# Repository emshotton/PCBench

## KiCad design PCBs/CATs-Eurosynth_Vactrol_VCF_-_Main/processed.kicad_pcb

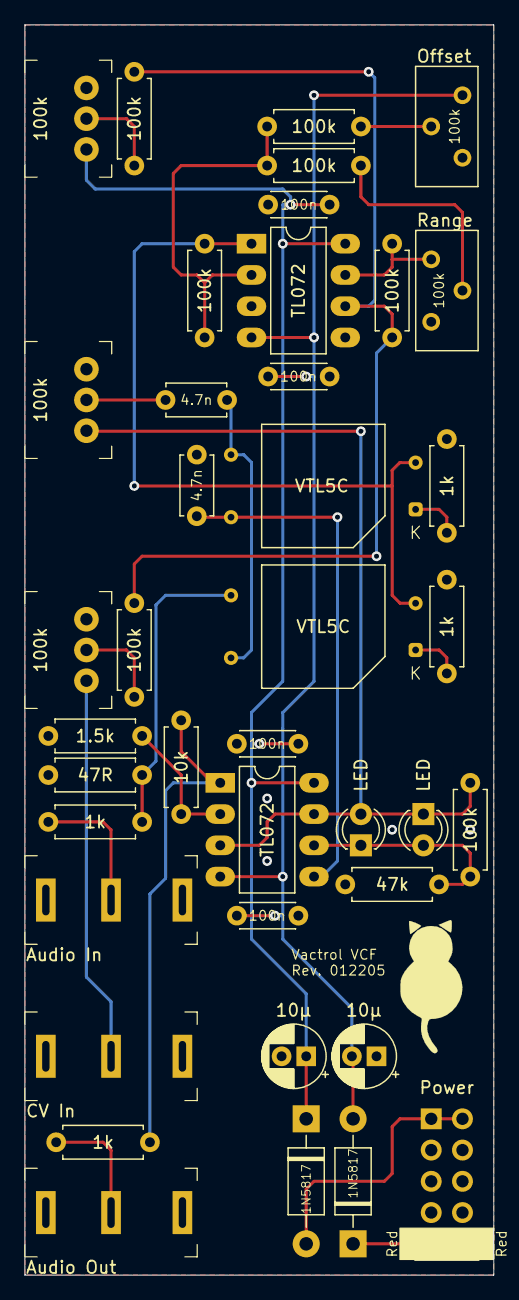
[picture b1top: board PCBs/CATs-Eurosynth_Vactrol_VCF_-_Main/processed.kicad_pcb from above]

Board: 2 copper layers, 38.1 x 101.6 mm, 40 parts (0 on the bottom side), 26 nets.

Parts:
C1, C2: 4.7n; C_Disc_D4.7mm_W2.5mm_P5.00mm
C3, C4: 10µ; CP_Radial_D5.0mm_P2.00mm
C5, C6, C7, C8: 100n; C_Disc_D4.3mm_W1.9mm_P5.00mm
D1, D2: LED; LED_D3.0mm
D3, D4: 1N5817; D_DO-41_SOD81_P10.16mm_Horizontal
J1: Audio In; Jack_3.5mm_QingPu_WQP-PJ323M
J2: Audio Out; Jack_3.5mm_QingPu_WQP-PJ323M
J3: Power; Power_2x5_Vertical
J4: CV In; Jack_3.5mm_QingPu_WQP-PJ323M
P1, P2, P3: 100k; Potentiometer_AlpsAlpine_RK0971110
R1, R3, R4, R12: 1k; R_Axial_DIN0207_L6.3mm_D2.5mm_P7.62mm_Horizontal
R2: 47R; R_Axial_DIN0207_L6.3mm_D2.5mm_P7.62mm_Horizontal
R5: 47k; R_Axial_DIN0207_L6.3mm_D2.5mm_P7.62mm_Horizontal
R6, R7, R8, R9, R13, R14, R15: 100k; R_Axial_DIN0207_L6.3mm_D2.5mm_P7.62mm_Horizontal
R10: 1.5k; R_Axial_DIN0207_L6.3mm_D2.5mm_P7.62mm_Horizontal
R11: 10k; R_Axial_DIN0207_L6.3mm_D2.5mm_P7.62mm_Horizontal
RV1, RV2: 100k; Potentiometer_Bourns_3296Y_Vertical
U1, U2: VTL5C; PerkinElmer_VTL5C
U3, U4: TL072; DIP-8_W7.62mm_LongPads

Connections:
+12V: C3.1, C5.1, C7.1, D3.1, P2.CW, U3.8, U4.8
-12V: C4.2, C6.2, C8.2, D4.2, RV1.3, U3.4, U4.4
GND: C2.1, C3.2, C4.1, C5.2, C6.1, C7.2, C8.1, J1.S, J1.TN, J2.S, J3.GND, J4.S, J4.TN, P1.CCW, P2.CCW, P3.CCW, R2.2, R3.1, R4.1, R5.1, R10.1, RV1.1, RV2.3, U3.3, U3.5
unnamed: C1.1, P1.W
unnamed: C1.2, U1.3, U2.4
unnamed: C2.2, U2.3, U4.5
unnamed: D1.1, D2.2, R5.2, R7.2, U4.6
unnamed: D1.2, D2.1, P1.CW, R7.1, U4.3, U4.7
unnamed: D3.2, J3.+12V
unnamed: D4.1, J3.-12V
unnamed: J1.T, R1.2
unnamed: J2.T, R12.1
unnamed: J4.T, P3.CW
unnamed: P2.W, R14.1
unnamed: P3.W, R15.1
unnamed: R1.1, R2.1, U1.4
unnamed: R3.2, U1.1
unnamed: R4.2, U2.1
unnamed: R6.1, R8.2, R9.2, U3.2
unnamed: R6.2, U1.2, U2.2, U3.1
unnamed: R8.1, RV1.2
unnamed: R9.1, RV2.2
unnamed: R10.2, R11.2, U4.2
unnamed: R11.1, R12.2, U4.1
unnamed: R13.1, R14.2, R15.2, U3.6
unnamed: R13.2, RV2.1, U3.7

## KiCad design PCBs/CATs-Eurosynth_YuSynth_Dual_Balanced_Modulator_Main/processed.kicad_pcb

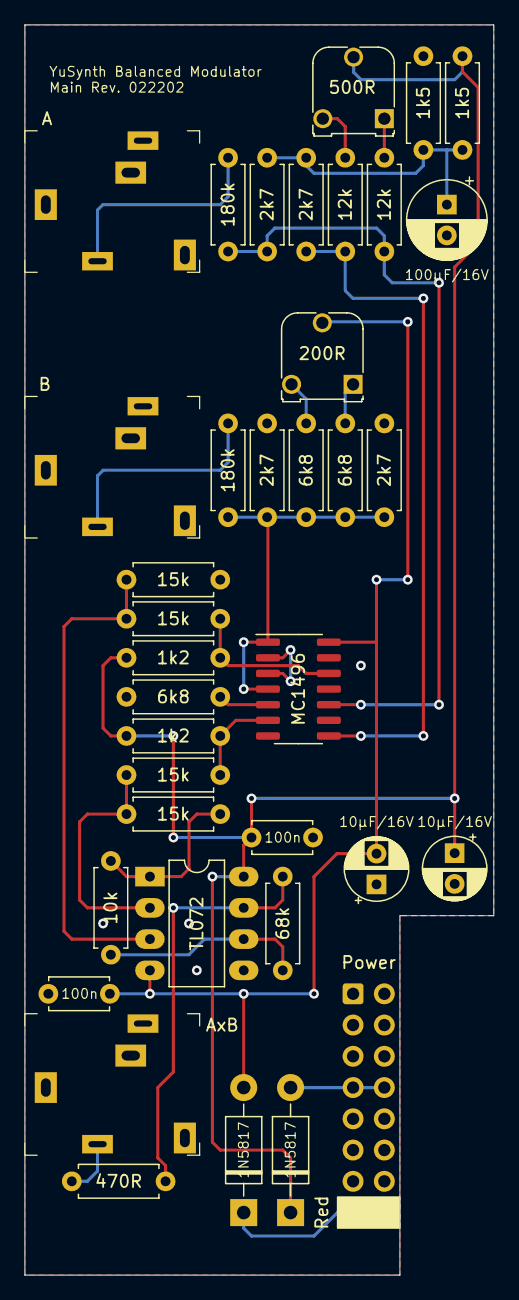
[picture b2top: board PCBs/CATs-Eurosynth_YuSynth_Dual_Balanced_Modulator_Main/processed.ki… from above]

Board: 2 copper layers, 38.1 x 101.6 mm, 37 parts (0 on the bottom side), 25 nets.

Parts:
C1: 100µF/16V; CP_Radial_D6.3mm_P2.50mm
C2, C3: 10µF/16V; CP_Radial_D5.0mm_P2.50mm
C4, C5: 100n; C_Disc_D4.7mm_W2.5mm_P5.00mm
D1, D2: 1N5817; D_DO-41_SOD81_P10.16mm_Horizontal
J1: Power; Power_2x8_Horizontal
J2: A; Jack_3.5mm_QingPu_WQP-PJ324M
J3: B; Jack_3.5mm_QingPu_WQP-PJ324M
J4: AxB; Jack_3.5mm_QingPu_WQP-PJ324M
R1, R2: 1k5; R_Axial_DIN0207_L6.3mm_D2.5mm_P7.62mm_Horizontal
R3, R4: 180k; R_Axial_DIN0207_L6.3mm_D2.5mm_P7.62mm_Horizontal
R5, R7, R8, R12: 2k7; R_Axial_DIN0207_L6.3mm_D2.5mm_P7.62mm_Horizontal
R6, R10, R14: 6k8; R_Axial_DIN0207_L6.3mm_D2.5mm_P7.62mm_Horizontal
R9, R11: 12k; R_Axial_DIN0207_L6.3mm_D2.5mm_P7.62mm_Horizontal
R13, R15: 1k2; R_Axial_DIN0207_L6.3mm_D2.5mm_P7.62mm_Horizontal
R16, R17, R18, R19: 15k; R_Axial_DIN0207_L6.3mm_D2.5mm_P7.62mm_Horizontal
R20: 10k; R_Axial_DIN0207_L6.3mm_D2.5mm_P7.62mm_Horizontal
R21: 68k; R_Axial_DIN0207_L6.3mm_D2.5mm_P7.62mm_Horizontal
R22: 470R; R_Axial_DIN0207_L6.3mm_D2.5mm_P7.62mm_Horizontal
RV1: 200R; Potentiometer_Runtron_RM-065_Vertical
RV2: 500R; Potentiometer_Runtron_RM-065_Vertical
U1: MC1496; SOIC-14_3.9x8.7mm_P1.27mm
U2: TL072; DIP-8_W7.62mm_LongPads

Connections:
+6V: C1.1, R1.1, R2.2, R7.2, R8.2
+12V: C2.1, C4.1, D1.1, R1.2, R13.1, R15.1, RV2.2, U2.8
+12VA: D1.2, J1.+12V
-12V: C3.2, C5.2, D2.2, RV1.2, U1.14, U2.4
-12VA: D2.1, J1.-12V
GND: C1.2, C2.2, C3.1, C4.2, C5.1, J1.GND, J2.S, J3.S, J4.S, R2.1, R5.2, R12.1, R14.2, R18.1, U2.5
In_A: J2.T, R3.2
In_B: J3.T, R4.1
unnamed: R3.1, R8.1, R9.2, U1.10
unnamed: R6.2, RV1.3
unnamed: R9.1, RV2.1
unnamed: R4.2, R5.1, R6.1, R10.1, R12.2, U1.1, U1.4
unnamed: R10.2, RV1.1
unnamed: R11.1, RV2.3
unnamed: R7.1, R11.2, U1.8
unnamed: R13.2, R16.1, U1.6
unnamed: R14.1, U1.5
unnamed: R15.2, R17.2, U1.12
unnamed: R16.2, R19.2, U2.2
unnamed: R17.1, R18.2, U2.3
unnamed: R19.1, R20.2, U2.1
unnamed: R20.1, R21.2, U2.6
unnamed: R21.1, R22.2, U2.7
unnamed: U1.2, U1.3
Out: J4.T, R22.1

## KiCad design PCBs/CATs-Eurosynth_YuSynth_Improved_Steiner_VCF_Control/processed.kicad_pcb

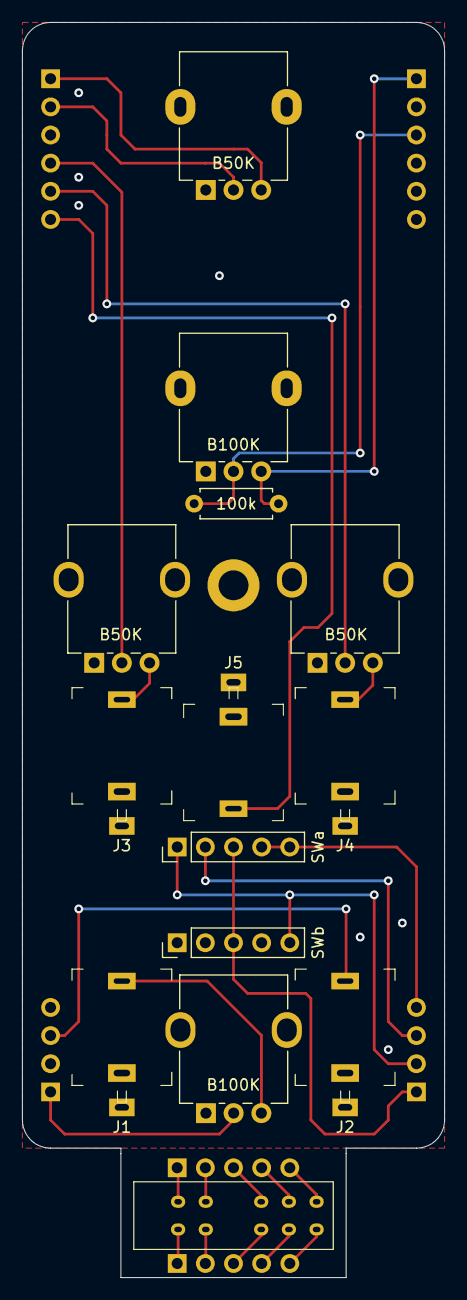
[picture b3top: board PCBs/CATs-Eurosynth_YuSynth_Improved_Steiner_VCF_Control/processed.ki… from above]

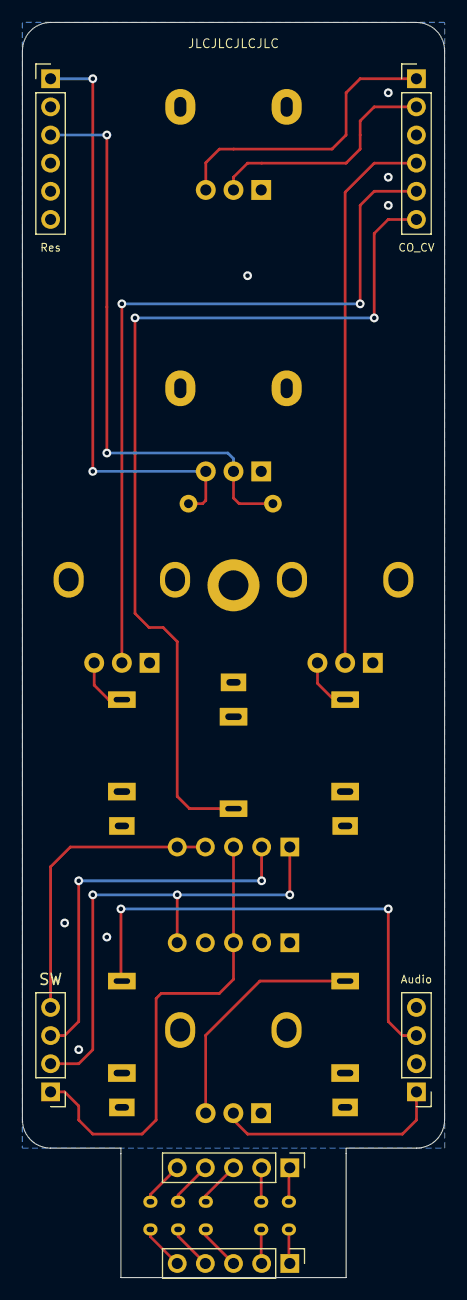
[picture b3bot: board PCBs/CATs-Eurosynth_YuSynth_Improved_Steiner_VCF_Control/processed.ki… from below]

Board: 2 copper layers, 38.1 x 113.3 mm, 21 parts (6 on the bottom side), 22 nets.

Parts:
H1: MountingHole_Pad; MountingHole_2.7mm_M2.5_DIN965_Pad
J1: Audio In; Jack_3.5mm_QingPu_WQP-PJ301M-12
J2: Audio Out; Jack_3.5mm_QingPu_WQP-PJ301M-12
J3: CV#1; Jack_3.5mm_QingPu_WQP-PJ301M-12
J4: CV#2; Jack_3.5mm_QingPu_WQP-PJ301M-12
J5: V/Oct; Jack_3.5mm_QingPu_WQP-PJ301M-12
J6, J12: SWb; PinHeader_1x05_P2.54mm_Vertical
J7, J13: SWa; PinHeader_1x05_P2.54mm_Vertical
J8: Audio; PinHeader_1x04_P2.54mm_Vertical
J9: SW; PinHeader_1x04_P2.54mm_Vertical
J10: CO_CV; PinHeader_1x06_P2.54mm_Vertical
J11: Res; PinHeader_1x06_P2.54mm_Vertical
R1: 100k; R_Axial_DIN0207_L6.3mm_D2.5mm_P7.62mm_Horizontal
RV1, RV5: B100K; Potentiometer_Alpha_RD901F-40-00D_Single_Vertical
RV2, RV3, RV4: B50K; Potentiometer_Alpha_RD901F-40-00D_Single_Vertical
SW1: Mode; SS24E01-G5

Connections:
AudioOut: J2.T, J8.3
GND: H1.1, J1.S, J2.S, J3.S, J4.S, J5.S, J8.2, J8.4, J10.3, J11.2, J11.4, J11.5, J11.6, RV1.1, RV2.1, RV3.1, RV4.1, RV5.1
unnamed: J1.T, RV1.3
unnamed: J3.T, RV3.3
unnamed: J4.T, RV2.3
unnamed: J12.1, SW1.1
unnamed: J12.2, SW1.2
unnamed: J12.3, SW1.3
unnamed: J12.4, SW1.4
unnamed: J12.5, SW1.5
unnamed: J13.1, SW1.6
unnamed: J13.2, SW1.7
unnamed: J13.3, SW1.8
unnamed: J13.4, SW1.9
unnamed: J13.5, SW1.10
Res_In: J11.1, R1.1, RV5.3
Res_Out: J11.3, R1.2, RV5.2
SW_A: J6.5, J7.1, J9.2
SW_B: J7.2, J9.3
SW_C: J7.4, J7.5, J9.4
SW_In: J6.3, J7.3, J9.1
vOct: J5.T, J10.6

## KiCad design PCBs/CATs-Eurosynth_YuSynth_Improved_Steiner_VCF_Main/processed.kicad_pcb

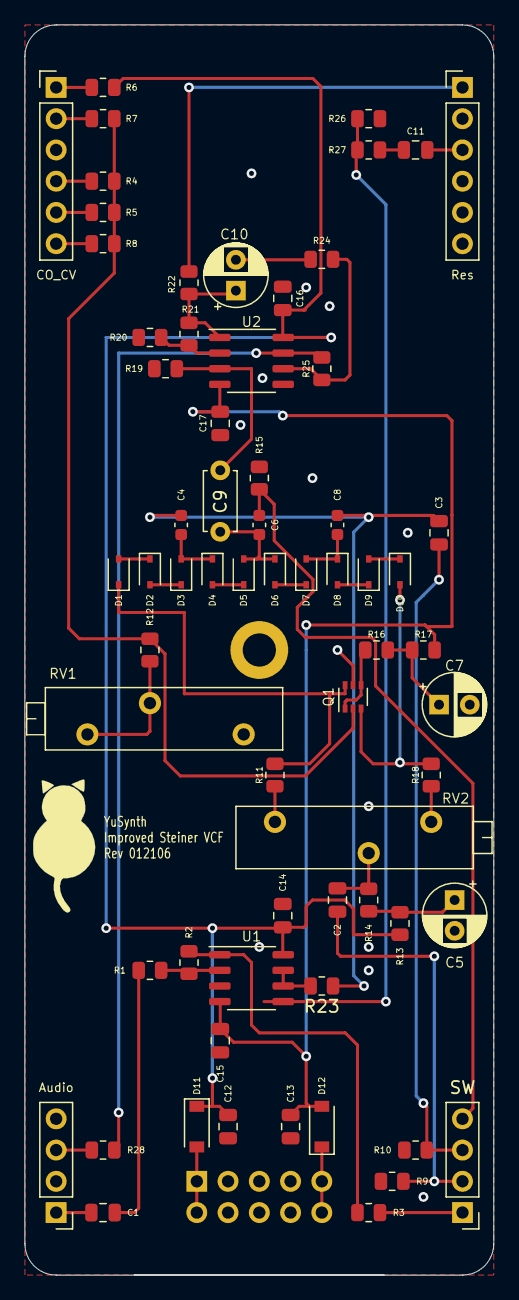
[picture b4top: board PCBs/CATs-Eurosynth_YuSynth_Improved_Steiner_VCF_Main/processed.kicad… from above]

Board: 2 copper layers, 38.1 x 101.6 mm, 68 parts (1 on the bottom side), 50 nets.

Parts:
C1, C11, C12, C13: 10uF; C_0805_2012Metric
C2, C3: 2.2uF; C_0805_2012Metric
C4, C6, C8: 1.5n; C_0603_1608Metric
C5, C7, C10: 47µF; CP_Radial_D5.0mm_P2.50mm
C9: 680n; C_Disc_D4.7mm_W2.5mm_P5.00mm
C14, C15, C16, C17: 100n; C_0805_2012Metric
D1, D2, D3, D4, D5, D6, D7, D8, D9, D10: 1N4148WS; D_SOD-323
D11, D12: B5819W; D_SOD-123
H1: MountingHole_Pad; MountingHole_2.7mm_M2.5_DIN965_Pad
J1: Power; PinHeader_2x05_P2.54mm_Vertical
J8: Audio; PinHeader_1x04_P2.54mm_Vertical
J9: SW; PinHeader_1x04_P2.54mm_Vertical
J10: CO_CV; PinHeader_1x06_P2.54mm_Vertical
J11: Res; PinHeader_1x06_P2.54mm_Vertical
Q1: BC847BDW1; SOT-363_SC-70-6
R1, R2, R24: 10k; R_0805_2012Metric
R3, R6, R21: 47k; R_0805_2012Metric
R4, R5, R8, R25, R27: 220k; R_0805_2012Metric
R7: 150k; R_0805_2012Metric
R9, R10: 180k; R_0805_2012Metric
R11, R18: 1.8k; R_0805_2012Metric
R12: 220R; R_0805_2012Metric
R13: 390; R_0805_2012Metric
R14, R15, R23, R28: 1k; R_0805_2012Metric
R16, R22: 3.9k; R_0805_2012Metric
R17: 82R; R_0805_2012Metric
R19: 2.2M; R_0805_2012Metric
R20: 22k; R_0805_2012Metric
R26: 1M; R_0805_2012Metric
RV1: 2k; Potentiometer_Bourns_3006P_Horizontal
RV2: 1k; Potentiometer_Bourns_3006P_Horizontal
U1, U2: TL072; SO-8_3.9x4.9mm_P1.27mm

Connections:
+12V: C12.1, C14.1, C16.1, D11.1, R6.2, R13.2, U1.8, U2.8
+12VA: D11.2, J1.1, J1.2
-12V: C13.2, C15.2, C17.2, D12.2, R17.1, U1.4, U2.4
-12VA: D12.1, J1.9, J1.10
AudioIn: C1.2, J8.1
AudioOut: J8.3, R28.2
CO_In: J10.1, R6.1
CO_Out: J10.2, R7.1
CV#1: J10.4, R4.2
CV#2: J10.5, R5.2
GND: C5.2, C7.2, C12.2, C13.1, C14.2, C15.1, C16.2, C17.1, H1.1, J1.3, J1.4, J1.5, J1.6, J1.7, J1.8, J8.2, J8.4, J10.3, J11.2, J11.4, J11.5, J11.6, Q1.5, R9.1, R10.1, R15.1, R19.1, R20.1, R26.1, RV1.1, U1.3, U2.5
unnamed: C1.1, R1.2
unnamed: C2.1, R14.1, RV2.2
unnamed: C3.1, C4.2, C8.2, R23.1
unnamed: C4.1, D3.2, D4.1
unnamed: C5.1, R13.1, R14.2
unnamed: C6.1, C9.2, D5.2, D6.1
unnamed: C7.1, R16.1, R17.2
unnamed: C8.1, D7.2, D8.1
unnamed: C9.1, R19.2, U2.3
unnamed: C10.1, R21.2, R22.2, U2.1
unnamed: C10.2, R24.2
unnamed: C11.2, R27.1
unnamed: D1.1, Q1.6, R11.1
unnamed: D1.2, D2.1
unnamed: D2.2, D3.1
unnamed: D4.2, D5.1
unnamed: D6.2, D7.1
unnamed: D8.2, D9.1
unnamed: D9.2, D10.1
unnamed: D10.2, Q1.3, R18.1
unnamed: Q1.1, Q1.4, R16.2
unnamed: Q1.2, R4.1, R5.1, R7.2, R8.1, R12.2
unnamed: R1.1, R2.2, U1.2
unnamed: R2.1, R3.2, U1.1
unnamed: R11.2, RV2.1
unnamed: R12.1, RV1.2, RV1.3
unnamed: R18.2, RV2.3
unnamed: R20.2, R21.1, U2.2
unnamed: R23.2, U1.6, U1.7
unnamed: R24.1, R25.2, U2.6
unnamed: R25.1, R28.1, U2.7
unnamed: R26.2, R27.2, U1.5
Res_In: J11.1, R22.1
Res_Out: C11.1, J11.3
SW_A: C2.2, J9.2, R9.2
SW_B: C3.2, J9.3, R10.2
SW_C: C6.2, J9.4, R15.2
SW_In: J9.1, R3.1
vOct: J10.6, R8.2

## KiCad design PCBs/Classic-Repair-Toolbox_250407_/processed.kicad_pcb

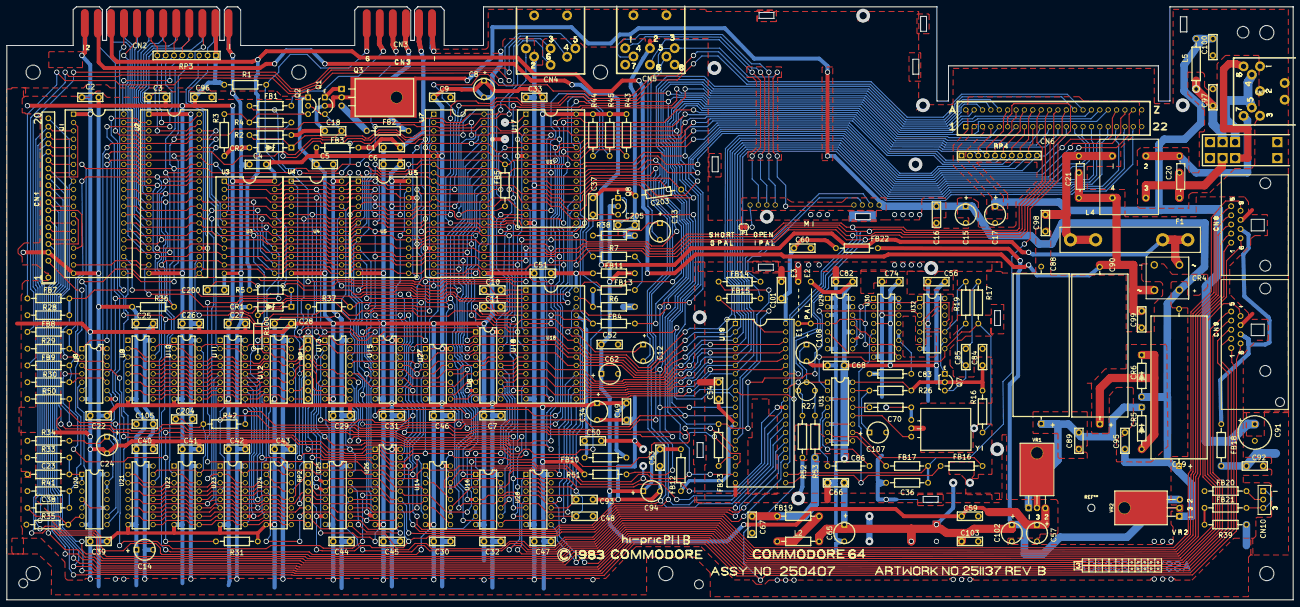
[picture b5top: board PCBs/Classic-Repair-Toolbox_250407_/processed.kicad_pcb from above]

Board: 2 copper layers, 390.0 x 179.8 mm, 215 parts (0 on the bottom side), 227 nets.

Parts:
C1, C2, C3, C4, C5, C6, C7, C9, C16, C18, C22, C25, C26, C27, C28, C29, C30, C31, C32, C33, C39, C40, C41, C42, C43, C44, C45, C46, C47, C49, C50, C51, C52, C53, C54, C56, C59, C60, C66, C67, C68, C74, C82, C84, C89, C92, C95, C96, C98, C99, C101, C103, C105, C200: .1; CAP_P5.08mm
C8, C12, C13, C14, C15, C17, C24, C34, C57, C62, C65, C94, C102, C107, C108: 10uF; CAP_ELYT_RADIAL_P5.08mm_SMALL_RING
C10, C11: 470pF; CAP_P5.08mm
C19: 2200uF; LARGE_ELECTROLYTIC_AXIAL_TH
C20, C21: .22; CAP_POLY_100V_TH_P5.08_and_P12.07mm
C23: 360pF; CAP_AXIAL_P12.7mm
C36: 20pF; RESISTOR
C37: 1000pF; CAP_P5.08mm
C38: 51pF; CAP_AXIAL_P12.7mm
C48, C93: 1800pF; CAP_P5.08mm
C70: 15pF 5%; RESISTOR
C83, C86: 82pF; RESISTOR
C85: .47; CAP_P5.08mm
C88: 1000uF; LARGE_ELECTROLYTIC_AXIAL_TH
C90: 470uF; LARGE_ELECTROLYTIC_AXIAL_TH
C91: 100uF; CAP_ELYT_RADIAL_P5.08mm
C97, C100: .22; CAP_P5.08mm
C203: 82pF; CAPACITOR_RADIAL_P13.97_L9.9_D3.6
C204: NC; CAP_P5.08mm
C205: 220pF; CAP_P5.08mm
CN1: KEYBOARD_20PIN_MALE; KEYBOARD_CON
CN2: USER_PORT_CON; EDGE_CON_24P
CN3: CASSETTE_PORT_CON; EDGE_CON_12P_TAPE
CN4: SERIAL_BUS_CON; SERIAL_CON_DIN6
CN5: AV_CONN; AV_CON_DIN8
CN6: EXPANSION_PORT
CN7: POWER_CON; POWER_CON_D7_250407
CN8, CN9: CONTROL_PORT; JOYPORT_DB9
CN10: LED_CONNECTOR; LED_CON
CR1: IN4371; ZENER_12.7mm
CR2: IN755; ZENER_12.7mm
CR4: BRIDGE_RECTIFIER
CR5, CR6: 1N4001; RECTIFIER_TH_P12.7mm
E2: JUMPER_WIRE_DASHED; JUMPER_WIRE
E3: JUMPER_WIRE
F1: 1A; FUSE
FB1, FB2, FB3, FB4, FB5, FB7, FB8, FB9, FB10, FB11, FB12, FB13, FB14, FB15, FB16, FB17, FB18, FB19, FB20, FB21, FB22, FB23: FERRITE_BEAD; FERRITE_BEAD_TH_P12.7mm
JP1: Jumper_NC_Small; SolderJumper-2_P1.3mm_Bridged_RoundedPad1.0x1.5mm
L2: 2.2uH; RESISTOR
L4: CHOKE
L5: 1.2uH; INDUCTOR_P15.24mm
M1: MODULATOR_LONGBOARD; MODULATOR_PORT_LONGBOARD
Q1, Q2, Q7, Q8: 2SC1815; Q_NPN_ECB
Q3: TP29B/2SD880; TO-220-3_Horizontal_TabDown_250407
R1, R43, R44, R45: 3K3; RESISTOR
R2, R51: 1.5K; RESISTOR
R3, R7: 10K; RESISTOR
R4, R6, R16, R28, R29, R30, R31, R36, R38, R100: 1K; RESISTOR
R5: 560; RESISTOR
R17, R37: 2K7; RESISTOR
R19: 15K; RESISTOR
R26, R53: 100; RESISTOR
R27: 500; POTMETER
R33, R34: 47K; RESISTOR
R35: 470K; RESISTOR
R39: 390; RESISTOR
R41, R50: 1M; RESISTOR
R42: 82; RESISTOR
R52: 330; RESISTOR
RP1, RP2: 33R isolated; RP_ARRAY_7WAY
RP3: 3K3 Bussed; RP_ARRAY_7WAY
RP4: 3K3 Bussed; RP_ARRAY_9WAY
SW1: POWER_SWITCH
U1: CIA_U1; DIP40
U2: CIA_U2; DIP40
U3, U4: 2364A; DIP24
U5: 2332A; DIP24
U6: 2114; DIP18
U7: 6510_MPU; DIP40
U8: 7406N; DIP14
U9, U10, U11, U12, U21, U22, U23, U24: 4164-2; DIP16
U13, U25: 74LS257; DIP16
U14: 74LS258; DIP16
U15: 74LS139; DIP16
U16, U28: 4066_U28; DIP14
U17: PLA_U17; DIP28
U18: 6581; DIP28
U19: VIC; DIP40
U20: 556; DIP14
U26: 74LS373; DIP20
U27: 7408_U27; DIP14
U29: 74LS74; DIP14
U30: 74LS193; DIP16
U31: 74LS629N; DIP16
U32: MC4044; DIP14
VR1: 7812; VREG_TO-220-3_Horizontal_TabDown
VR2: 7805; VREG_TO-220-3_Horizontal_TabDown
Y1: Crystal; CRYSTAL

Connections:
+5V: C2.1, C3.2, C4.2, C5.2, C6.2, C7.1, C8.1, C9.1, C14.1, C17.1, C22.1, C25.1, C26.1, C27.1, C28.1, C29.2, C30.1, C31.2, C32.2, C33.1, C34.1, C39.2, C40.1, C41.1, C42.1, C43.1, C44.2, C45.1, C46.1, C47.1, C49.1, C91.1, C92.1, C96.2, C100.2, CN1.4, CN2.2, CN6.2, CN6.3, FB3.2, FB10.2, FB18.1, L5.1, R1.1, R28.2, R29.2, R30.2, R31.2, R33.1, R34.1, R35.1, R36.1, R39.1, R41.1, R43.1, R44.1, R45.1, R50.1, R51.2, RP3.1, RP4.1, U1.20, U2.20, U3.24, U4.24, U5.21, U5.24, U6.18, U7.6, U8.14, U9.8, U10.8, U11.8, U12.8, U13.16, U14.16, U15.16, U16.14, U17.28, U20.4, U20.10, U20.14, U21.8, U22.8, U23.8, U24.8, U25.16, U26.20, U27.1, U27.14, U28.14
+9V_UNREG: C15.1, C16.1, C18.1, C19.1, C95.1, CR4.1, CR6.2, M1.1, Q1.2, Q3.2, R2.1, VR2.1
+12V: C52.1, C53.1, C57.1, C59.1, C62.1, C94.1, FB11.2, FB12.2, Q8.2, VR1.2
/5V_FB3: C1.1, CN3.B,2, FB3.1
/5V_joyport: CN8.7, CN9.7, FB18.2
/9VAC: C20.2, L4.3, SW1.1
/9VAC~: C21.2, C90.2, C99.2, CN2.10, CR4.4, L4.4, R5.1
/60Hz: R37.2, U1.19, U2.19, U27.3
/250407_sheet2/AEC: U8.3, U14.15, U16.5, U16.6, U16.12, U16.13, U19.16, U26.1, U27.4, U27.12
/250407_sheet2/AUDIO_IN: C12.2, CN5.5
/250407_sheet2/AUDIO_OUT: C13.2, CN5.3, M1.4
/250407_sheet2/BA: CN6.12, U17.26, U19.12, U27.9
/250407_sheet2/CHROMA: FB14.2, M1.3
/250407_sheet2/CHROMA_O: CN5.6, M1.7
/250407_sheet2/COMP_O: CN5.4, M1.5
/250407_sheet2/GR\~W: U6.10, U17.13
/250407_sheet2/LUMA: FB15.2, M1.2
/250407_sheet2/LUMA_O: CN5.1, M1.6
/250407_sheet2/MA0: RP2.4, U9.5, U10.5, U11.5, U12.5, U21.5, U22.5, U23.5, U24.5
/250407_sheet2/MA1: RP2.8, U9.7, U10.7, U11.7, U12.7, U21.7, U22.7, U23.7, U24.7
/250407_sheet2/MA2: RP2.6, U9.6, U10.6, U11.6, U12.6, U21.6, U22.6, U23.6, U24.6
/250407_sheet2/MA3: RP2.2, U9.12, U10.12, U11.12, U12.12, U21.12, U22.12, U23.12, U24.12
/250407_sheet2/MA4: RP1.4, U9.11, U10.11, U11.11, U12.11, U21.11, U22.11, U23.11, U24.11
/250407_sheet2/MA5: RP1.6, U9.10, U10.10, U11.10, U12.10, U21.10, U22.10, U23.10, U24.10
/250407_sheet2/MA6: RP1.2, U9.13, U10.13, U11.13, U12.13, U21.13, U22.13, U23.13, U24.13
/250407_sheet2/MA7: RP1.8, U9.9, U10.9, U11.9, U12.9, U21.9, U22.9, U23.9, U24.9
/250407_sheet2/VA0: RP2.3, U19.24, U25.12, U26.7
/250407_sheet2/VA1: RP2.7, U19.25, U25.9, U26.13
/250407_sheet2/VA2: RP2.5, U19.26, U25.7, U26.8
/250407_sheet2/VA3: RP2.1, U19.27, U25.4, U26.14
/250407_sheet2/VA4: RP1.3, U13.12, U17.20, U19.28, U26.17
/250407_sheet2/VA5: RP1.5, U13.7, U17.21, U19.29, U26.18
/250407_sheet2/VA6: RP1.1, U13.4, U14.4, U26.4
/250407_sheet2/VA6': U14.13, U14.14, U19.30
/250407_sheet2/VA7: RP1.7, U13.9, U14.7, U26.3
/250407_sheet2/VA7': U14.10, U14.11, U19.31
/250407_sheet2/~AEC: R31.1, U8.4, U13.15, U17.25, U25.15
/250407_sheet2/~BASIC: U3.20, U17.17
/250407_sheet2/~CASRAM: R42.2, U17.18
/250407_sheet2/~CASRAM': C204.2, R42.1, U9.15, U10.15, U11.15, U12.15, U21.15, U22.15, U23.15, U24.15
/250407_sheet2/~CAS: C203.2, U13.1, U14.1, U17.9, U19.19, U25.1
/250407_sheet2/~CHAROM: U5.20, U17.15
/250407_sheet2/~CIAS: U15.7, U15.15
/250407_sheet2/~COLOR: U15.6, U27.13
/250407_sheet2/~DMA: CN6.13, RP4.10, U27.5, U27.10
/250407_sheet2/~EXROM: CN6.9, RP4.9, U17.23
/250407_sheet2/~GAME: CN6.8, RP4.7, U17.22
/250407_sheet2/~I\O: U15.1, U17.12
/250407_sheet2/~KERNAL: U4.20, U17.16
/250407_sheet2/~RAS: U9.4, U10.4, U11.4, U12.4, U19.18, U21.4, U22.4, U23.4, U24.4, U26.11
/250407_sheet2/~RESET': CN6.C, FB4.1
/250407_sheet2/~ROMH: CN6.B, U17.10
/250407_sheet2/~ROML: CN6.11, U17.11
/250407_sheet2/~SID: U15.5, U18.8
/250407_sheet2/~VIC: U15.4, U19.10
/'9VAC~: CN2.11, CR4.2, F1.1
/+Vc: C56.1, C67.1, C68.1, C74.1, C82.1, C84.1, E2.1, FB19.2, Q7.2, R16.1, R26.1, R53.1, U29.10, U29.13, U29.14, U30.4, U30.15, U30.16, U31.16, U32.14
/ATN: CN4.3, FB7.1
/ATN': CN2.9, FB7.2, R28.1, U8.12
/ATN_OUT: U2.5, U8.13
/BTNB: CN1.16, CN8.6, U1.6
/CASS_MOTOR: R4.2, U7.24
/CASS_PWR: CN3.C,3, FB2.1
/CASS_RD: CN3.D,4, CN4.1, RP3.4, U1.24
/CASS_SENSE: CN3.F,6, R1.2, U7.25
/CASS_WRT: FB1.2, U7.26
/CASS_WRT': CN3.E,5, FB1.1
/CLK: CN4.4, FB9.1
/CLK': FB9.2, R30.1, U2.8, U8.10
/CLK_OUT: U2.6, U8.11
/CNT1: CN2.4, RP3.5, U1.40
/CNT2: CN2.6, RP3.7, U2.40
/COL0: CN1.13, CN8.1, U1.2
/COL1: CN1.19, CN8.2, U1.3
/COL2: CN1.18, CN8.3, U1.4
/COL3: CN1.17, CN8.4, U1.5
/COL5: CN1.15, U1.7
/COL6: CN1.14, U1.8, U28.6, U28.12
/COL7: CN1.20, U1.9, U28.5, U28.13
/DATA: CN4.5, FB8.1
/DATA': FB8.2, R29.1, U2.9, U8.2
/DATA_OUT: U2.7, U8.1
/F_DIV: U29.11, U30.6
/GND_LED: CN10.2, FB20.2
/JOYA0: CN1.12, CN9.1, U1.10
/JOYA1: CN1.11, CN9.2, U1.11
/JOYA2: CN1.10, CN9.3, U1.12
/JOYA3: CN1.5, CN9.4, U1.13
/LED+: CN10.1, CN10.3, FB21.2
/PA2: CN2.M, U2.4
/PB0: CN2.C, U2.10
/PB1: CN2.D, U2.11
/PB2: CN2.E, U2.12
/PB3: CN2.F, U2.13
/PB4: CN2.H, U2.14
/PB5: CN2.J, U2.15
/PB6: CN2.K, U2.16
/PB7: CN2.L, U2.17
/PH2_FB: FB5.2, U7.39
/POTAX: CN9.9, U28.8
/POTAY: CN9.5, U28.11
/POTBX: CN8.9, U28.1
/POTBY: CN8.5, U28.4
/ROW5: CN1.7, U1.15
/ROW6: CN1.6, U1.16
/ROW7: CN1.9, U1.17
/SP1: CN2.5, RP3.6, U1.39
/SP2: CN2.7, RP3.8, U2.39
/TRIGA: C38.1, R35.2, U20.6
/jumper_select: E2.2, E3.2, U29.4, U30.1, U30.10
/~FLAG2: CN2.B, RP3.2, U2.24
/~PC2: CN2.8, U2.18
/~RESTORE: C38.2, CN1.3, R41.2
A0: CN6.Y, U1.38, U2.38, U3.8, U4.8, U5.8, U6.5, U7.7, U18.9, U25.13, U26.6
A1: CN6.X, U1.37, U2.37, U3.7, U4.7, U5.7, U6.6, U7.8, U18.10, U25.10, U26.12
A2: CN6.W, U1.36, U2.36, U3.6, U4.6, U5.6, U6.7, U7.9, U18.11, U25.6, U26.9
A3: CN6.V, U1.35, U2.35, U3.5, U4.5, U5.5, U6.4, U7.10, U18.12, U25.3, U26.15
A4: CN6.U, U3.4, U4.4, U5.4, U6.3, U7.11, U13.13, U18.13, U26.16
A5: CN6.T, U3.3, U4.3, U5.3, U6.2, U7.12, U13.6, U26.19
A6: CN6.S, U3.2, U4.2, U5.2, U6.1, U7.13, U13.3, U26.5
A7: CN6.R, U3.1, U4.1, U5.1, U6.17, U7.14, U13.10, U26.2
A8: CN6.P, U3.23, U4.23, U5.23, U6.16, U7.15, U15.14, U19.32, U25.14
A9: CN6.N, U3.22, U4.22, U5.22, U6.15, U7.16, U15.13, U19.33, U25.11
A10: CN6.M, U3.19, U4.19, U5.19, U7.17, U15.2, U19.34, U25.5
A11: CN6.L, U3.18, U4.18, U5.18, U7.18, U15.3, U19.23, U25.2
A12: CN6.K, RP4.8, U3.21, U4.21, U7.19, U13.14, U17.27
A13: CN6.J, RP4.6, U7.20, U13.5, U17.2
A14: CN6.H, RP4.5, U7.22, U13.2, U17.3
A15: CN6.F, RP4.4, U7.23, U13.11, U17.4
BTNA\~LP: CN1.8, CN9.6, U1.14, U19.9
CAEC: U7.5, U27.6
CAN+5V: C65.1, C66.1, C102.1, C103.1, FB22.2, L2.1, VR2.2
D0: CN6.21, U1.33, U2.33, U3.9, U4.9, U5.9, U7.37, U16.11, U18.15, U19.7, U21.2, U21.14
D1: CN6.20, U1.32, U2.32, U3.10, U4.10, U5.10, U7.36, U9.2, U9.14, U16.8, U18.16, U19.6
D2: CN6.19, U1.31, U2.31, U3.11, U4.11, U5.11, U7.35, U16.4, U18.17, U19.5, U22.2, U22.14
D3: CN6.18, U1.30, U2.30, U3.13, U4.13, U5.13, U7.34, U10.2, U10.14, U16.1, U18.18, U19.4
D4: CN6.17, U1.29, U2.29, U3.14, U4.14, U5.14, U7.33, U18.19, U19.3, U23.2, U23.14
D5: CN6.16, U1.28, U2.28, U3.15, U4.15, U5.15, U7.32, U11.2, U11.14, U18.20, U19.2
D6: CN6.15, U1.27, U2.27, U3.16, U4.16, U5.16, U7.31, U18.21, U19.1, U24.2, U24.14
D7: CN6.14, U1.26, U2.26, U3.17, U4.17, U5.17, U7.30, U12.2, U12.14, U18.22, U19.39
DOT_CLOCK: C36.1, CN6.6, FB17.2, U19.22
Earth: C1.2, C2.2, C3.1, C4.1, C5.1, C6.1, C7.2, C8.2, C9.2, C14.2, C15.2, C16.2, C17.2, C19.2, C22.2, C23.2, C24.2, C25.2, C26.2, C27.2, C28.2, C29.1, C30.2, C31.1, C32.1, C33.2, C34.2, C36.2, C37.2, C39.1, C40.2, C41.2, C42.2, C43.2, C44.1, C45.2, C46.2, C47.2, C48.2, C49.2, C50.2, C51.2, C52.2, C53.2, C54.2, C56.2, C57.2, C59.2, C60.2, C62.2, C65.2, C66.2, C67.2, C68.2, C74.2, C82.2, C83.2, C84.2, C88.2, C89.2, C91.2, C92.2, C93.2, C94.2, C95.2, C96.1, C97.1, C98.2, C99.1, C100.1, C101.2, C102.2, C103.2, C105.1, C107.2, C108.2, C200.2, C203.1, C204.1, C205.2, CN1.1, CN2.1, CN2.12, CN2.A, CN2.N, CN3.A,1, CN4.2, CN5.2, CN6.1, CN6.22, CN6.A, CN6.Z, CN7.1, CN7.2, CN7.3, CN8.8, CN9.8, CR1.2, CR2.2, CR4.3, E3.1, FB20.1, JP1.2, Q2.1, R3.2, R6.1, R38.1, R52.2, U1.1, U2.1, U3.12, U4.12, U5.12, U6.9, U7.21, U8.7, U9.16, U10.16, U11.16, U12.16, U13.8, U14.8, U15.8, U16.7, U17.14, U17.19, U18.14, U19.20, U20.7, U21.16, U22.16, U23.16, U24.16, U25.8, U26.10, U27.7, U28.7, U29.1, U29.2, U29.3, U29.7, U30.8, U30.14, U31.3, U31.6, U31.8, U31.9, U31.11, U31.14, U32.7, VR1.3, VR2.3, Y1.3
unnamed: C10.1, U18.1
unnamed: C10.2, U18.2
unnamed: C11.1, U18.3
unnamed: C11.2, U18.4
unnamed: C12.1, U18.26
unnamed: C13.1, C205.1, Q8.1, R38.2
unnamed: C18.2, CR2.1, Q1.3, Q2.2, R2.2
unnamed: C20.1, CN7.7, L4.2
unnamed: C21.1, C98.1, F1.2, L4.1
unnamed: C23.1, R33.2, U20.1, U20.2
unnamed: C24.1, R34.2, U20.12, U20.13
unnamed: C37.1, Q8.3, R7.1
unnamed: C50.1, FB10.1, U18.25
unnamed: C51.1, FB11.1, U18.28
unnamed: C54.1, FB12.1, U19.13
unnamed: C70.1, Y1.2
unnamed: C70.2, U31.13
unnamed: C83.1, U30.11, U30.12
unnamed: C85.1, R17.2
unnamed: C85.2, Q7.3, R19.1
unnamed: C86.1, U31.5
unnamed: C86.2, U31.4
unnamed: C88.1, C89.1, CR5.1, VR1.1
unnamed: C90.1, CR5.2, CR6.1
unnamed: C97.2, L5.2, SW1.4
unnamed: C60.1, C101.1, FB22.1, U19.40
unnamed: C105.2, R50.2, U20.8
unnamed: C107.1, R26.2, U31.15
unnamed: C108.1, R27.3, U31.1
unnamed: C200.1, CR1.1, R5.2, R100.1
unnamed: CN6.7, U15.10
unnamed: CN6.10, U15.9
unnamed: CN7.4, CN7.5, SW1.5
unnamed: CN7.6, SW1.2
unnamed: FB2.2, Q3.3
unnamed: FB13.1, R6.2, U18.27
unnamed: FB13.2, R7.2
unnamed: FB14.1, U19.14
unnamed: FB15.1, U19.15
unnamed: FB16.1, U31.10
unnamed: FB17.1, U31.7
unnamed: FB19.1, L2.2
unnamed: FB21.1, R39.2
unnamed: FB23.1, U19.17
unnamed: JP1.1, M1.8
unnamed: Q1.1, Q3.1
unnamed: Q2.3, R3.1, R4.1
unnamed: Q7.1, U32.9
unnamed: R16.2, R17.1, U31.2, U32.8
unnamed: R19.2, U32.5, U32.10
unnamed: R27.1, R53.2
unnamed: R27.2, R52.1
unnamed: R37.1, R100.2, U27.2
unnamed: U14.6, U14.9
unnamed: U14.3, U14.12
unnamed: U6.11, U16.2, U19.35
unnamed: U6.12, U16.3, U19.36
unnamed: U6.13, U16.9, U19.37
unnamed: U6.14, U16.10, U19.38
unnamed: U8.5, U20.5
unnamed: U8.9, U20.9
unnamed: U6.8, U27.11
unnamed: U29.5, U30.9
unnamed: U29.9, U32.1
unnamed: U29.8, U29.12
unnamed: U31.12, Y1.1
unnamed: U32.2, U32.11
unnamed: U32.4, U32.13
PHI0: FB23.2, U7.1, U32.3
PHI2: CN6.E, FB5.1, U1.25, U2.25, U18.6
PHI_COLOR: FB16.2, U19.21, U30.5
POTX: C48.1, U18.24, U28.2, U28.9
POTY: C93.1, U18.23, U28.3, U28.10
RDY: U7.2, U27.8
R\~W: CN6.5, R51.1, U1.22, U2.22, U7.38, U9.3, U10.3, U11.3, U12.3, U17.24, U18.7, U19.11, U21.3, U22.3, U23.3, U24.3
~CHAREN: R43.2, U7.27, U17.6
~CIA1: U1.23, U15.12
~CIA2: U2.23, U15.11
~HIRAM: R44.2, U7.28, U17.7
~IRQ: CN6.4, RP4.3, U1.21, U7.3, U19.8
~LORAM: R45.2, U7.29, U17.8
~NMI: CN6.D, RP3.3, U2.21, U7.4, U8.6
~RESET: CN2.3, CN4.6, FB4.2, R36.2, U1.34, U2.34, U7.40, U8.8, U18.5
~VA14: U2.2, U14.2, U17.5
~VA15: U2.3, U14.5

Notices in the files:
PCBs/Classic-Repair-Toolbox_250407_/processed.kicad_pcb:
Licensed under CERN OHL v.1.2
PCBs/Classic-Repair-Toolbox_Open128/processed.kicad_pcb:
https://creativecommons.org/licenses/by-sa/4.0
CC BY-SA 4.0
